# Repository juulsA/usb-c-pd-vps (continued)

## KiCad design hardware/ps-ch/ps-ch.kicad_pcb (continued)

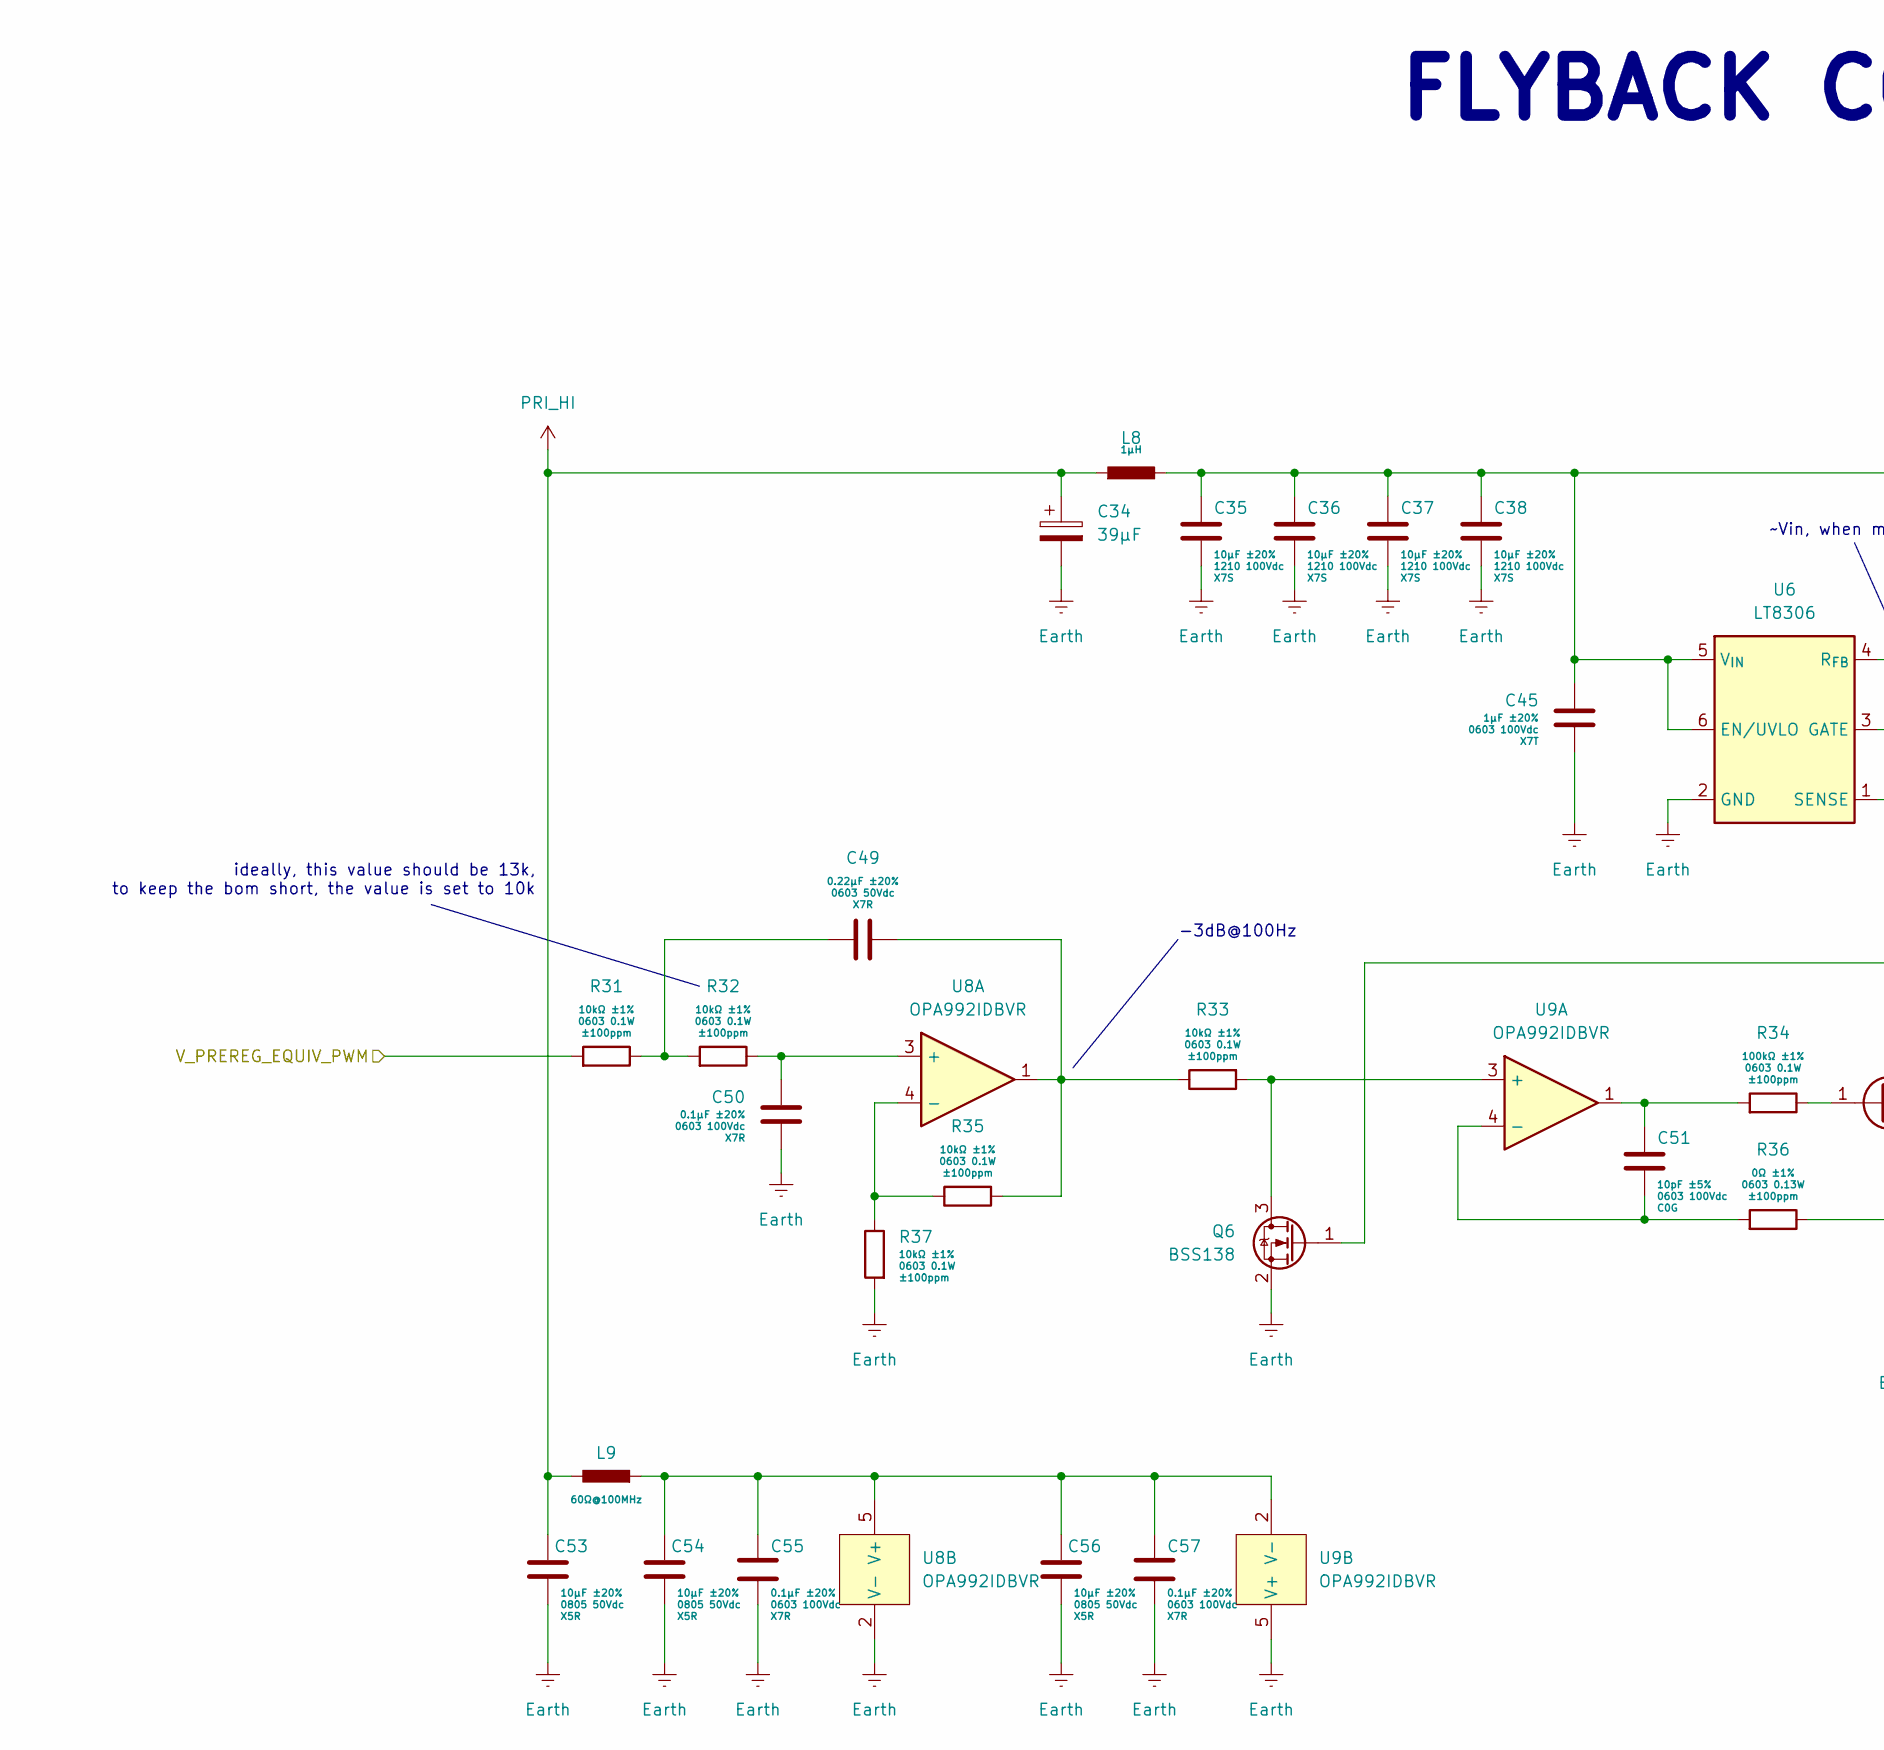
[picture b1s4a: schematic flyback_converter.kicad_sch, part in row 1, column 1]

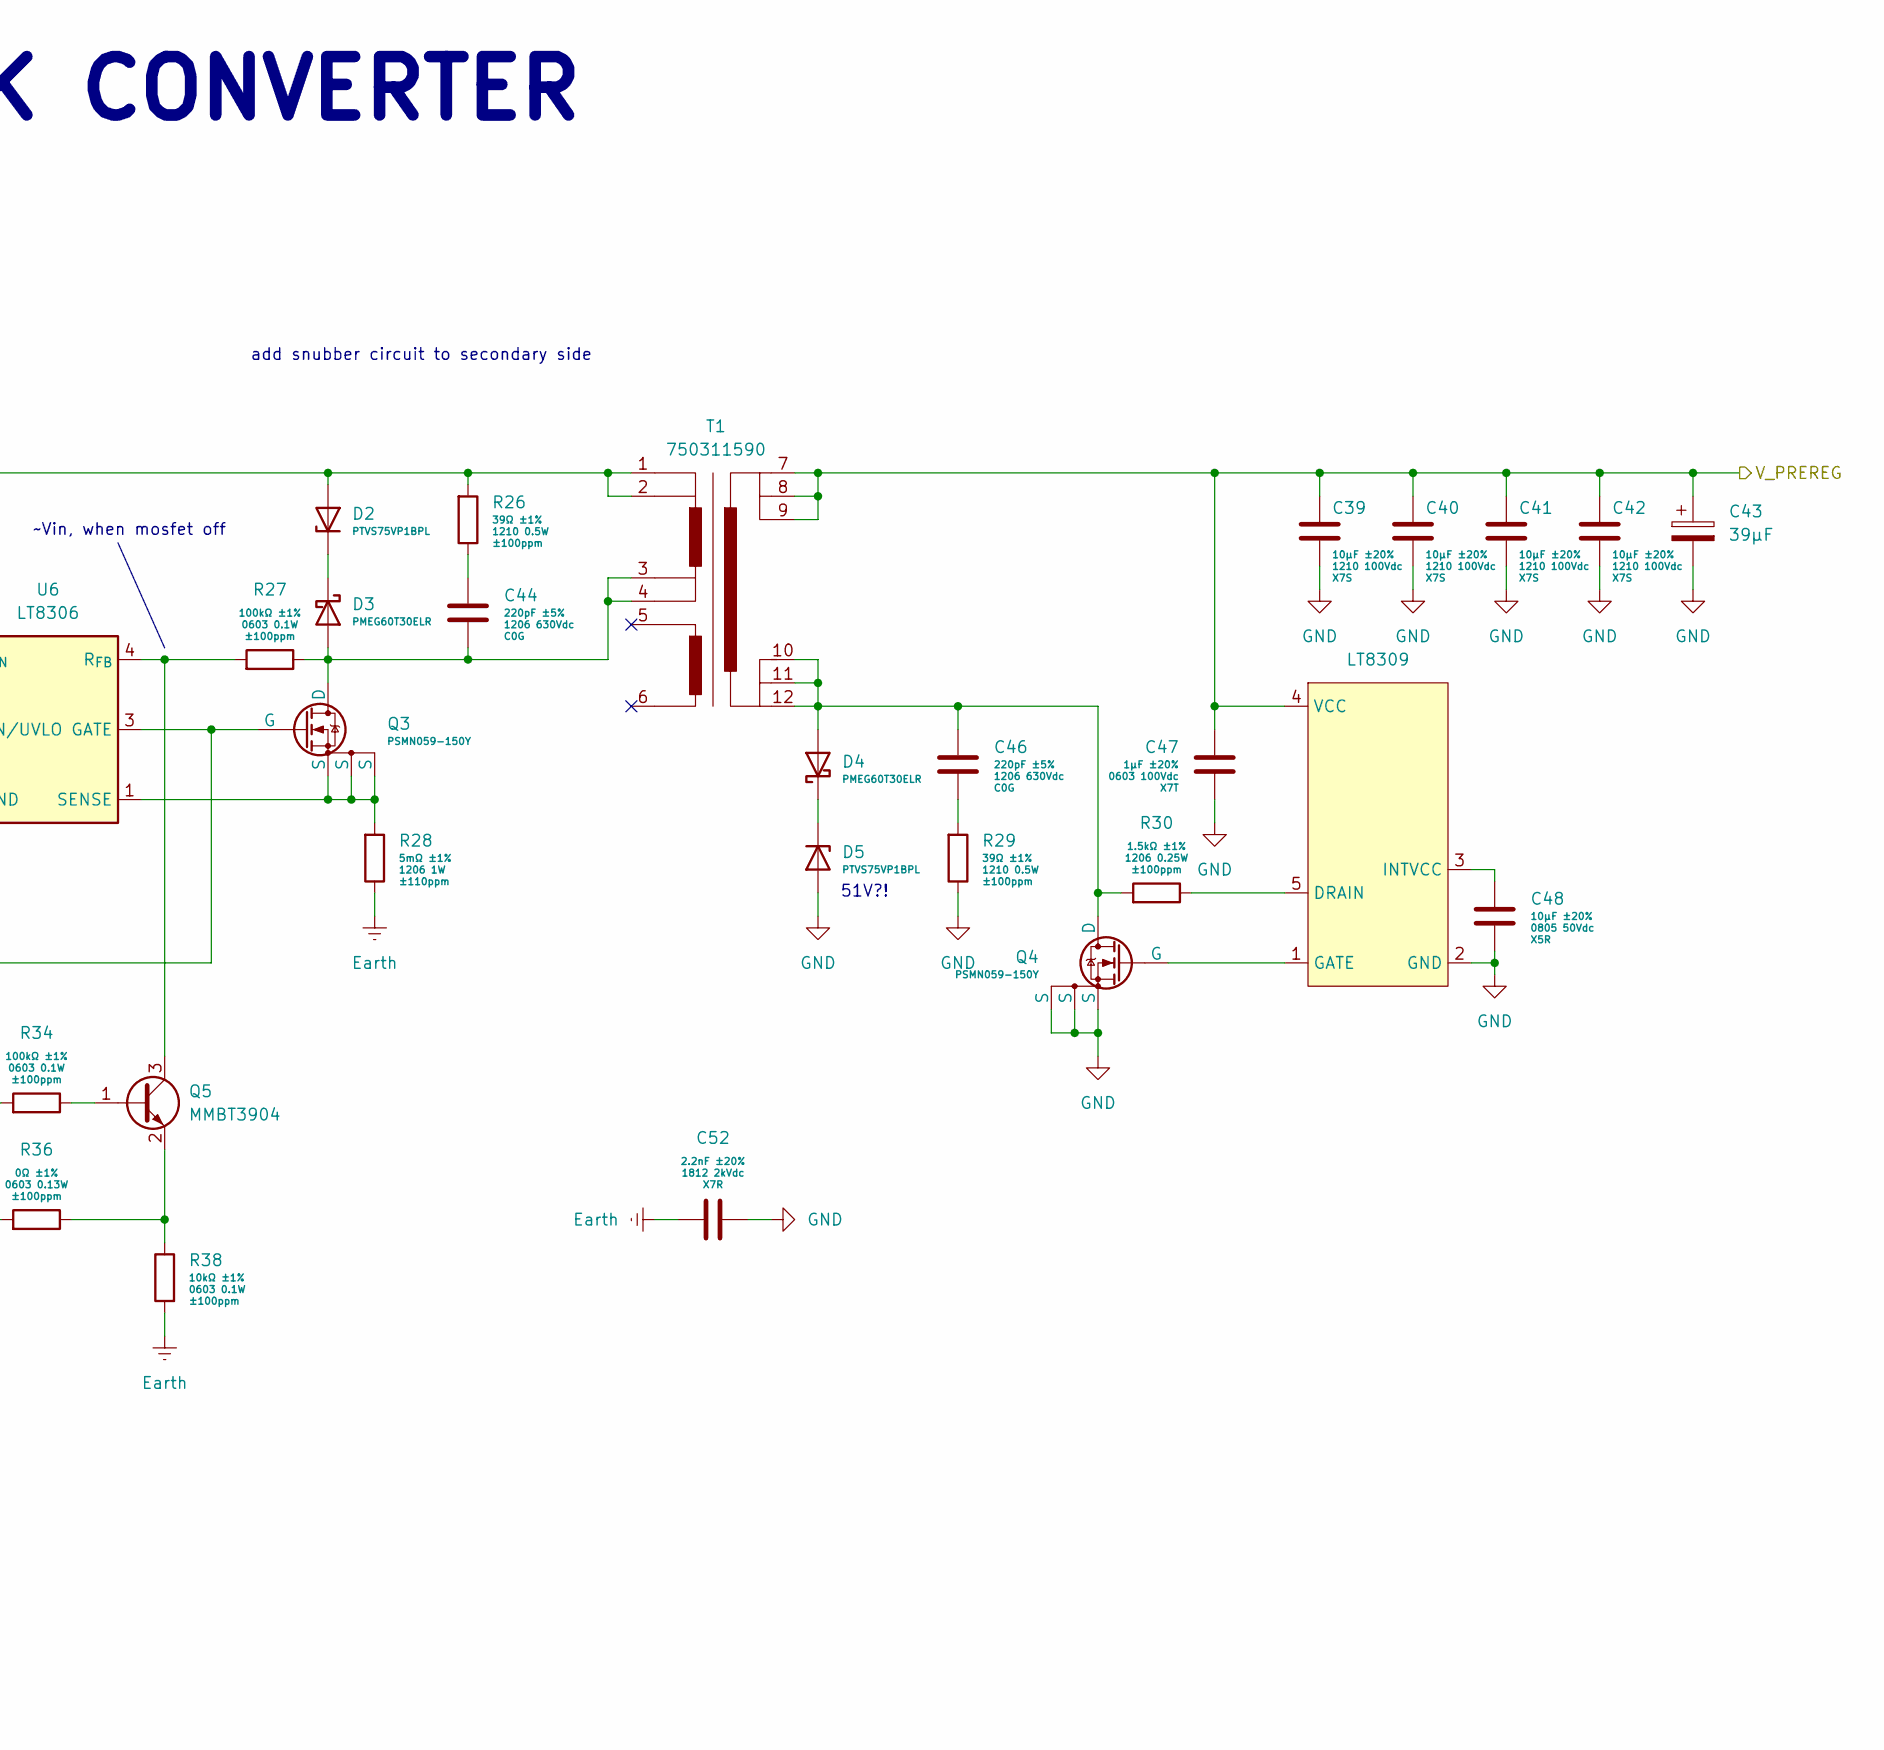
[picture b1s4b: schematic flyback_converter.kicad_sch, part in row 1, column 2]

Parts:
C34, C43: 39µF; CP_Elec_8x11.9; Manufacturer Part Number 875075855005
C35, C36, C37, C38, C39, C40, C41, C42: 10μF 1210 100Vdc X7S ±20%; C_1210_3225Metric; Manufacturer Part Number GRM32EC72A106ME05
C44, C46: 220pF 1206 630Vdc C0G ±5%; C_1206_3216Metric; Manufacturer Part Number GRM31A5C2J221JW01
C45, C47: 1μF 0603 100Vdc X7T ±20%; C_0603_1608Metric; Manufacturer Part Number GRM188D72A105ME01
C48, C53, C54, C56: 10μF 0805 50Vdc X5R ±20%; C_0805_2012Metric; Manufacturer Part Number GRM21BR61H106ME43
C49: 0.22μF 0603 50Vdc X7R ±20%; C_0603_1608Metric; Manufacturer Part Number GRM188R71H224MAC4
C50, C55, C57: 0.1μF 0603 100Vdc X7R ±20%; C_0603_1608Metric; Manufacturer Part Number GRM188R72A104MA35
C51: 10pF 0603 100Vdc C0G ±5%; C_0603_1608Metric; Manufacturer Part Number GCM1885C2A100JA16
C52: 2.2nF 1812 2kVdc X7R ±20%; C_1812_4532Metric; Manufacturer Part Number GR443QR73D222KW01
D2, D5: PTVS75VP1BPL; D_SOD-128; Manufacturer Part Number PTVS75VP1BPL
D3, D4: PMEG60T30ELR; Nexperia_CFP3_SOD-123W; Manufacturer Part Number PMEG60T30ELRX
L8: 1µH; WE-HCI_5040; Manufacturer Part Number 744316100
L9: 60Ω@100MHz; L_0603_1608Metric; Manufacturer Part Number 74279228600
Q3, Q4: PSMN059-150Y; SOT669; Manufacturer Part Number PSMN059-150Y,115
Q5: MMBT3904; SOT-23
Q6: BSS138; SOT-23
R26, R29: 39Ω 1210 0.5W ±1% ±100ppm/°C; R_1210_3225Metric; Manufacturer Part Number AC1210FR-0739RL
R27, R34: 100kΩ 0603 0.1W ±1% ±100ppm/°C; R_0603_1608Metric; Manufacturer Part Number AC0603FR-07100KL
R28: 5mΩ 1206 1W ±1% ±110ppm/°C; R_1206_3216Metric; Manufacturer Part Number WSLP12065L000FEA
R30: 1.5kΩ 1206 0.25W ±1% ±100ppm/°C; R_1206_3216Metric; Manufacturer Part Number AC1206FR-071K5L
R31, R32, R33, R35, R37, R38: 10kΩ 0603 0.1W ±1% ±100ppm/°C; R_0603_1608Metric; Manufacturer Part Number AC0603FR-0710KL
R36: 1kΩ 0603 0.1W ±1% ±100ppm/°C; R_0603_1608Metric; Manufacturer Part Number AC0603FR-070RL
T1: 750311590; EFD25; Manufacturer Part Number 750311590
U6: LT8306; TSOT-23-6
U7: LT8309; SOT-23-5; Manufacturer Part Number LT8309IS5#TRPBF
U8, U9: OPA992IDBVR; SOT-23-5; Manufacturer Part Number OPA992IDBVR

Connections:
/Flyback Converter/V_PREREG_EQUIV_PWM: R31.2; also elsewhere on the board
Earth: C34.2, C35.1, C36.1, C37.1, C38.1, C45.1, C50.1, C52.2, C53.1, C54.1, C55.1, C56.1, C57.1, Q6.2 (S), R28.1, R37.2, R38.2, U6.2 (GND), U8.2 (V-), U9.5 (V+); also elsewhere on the board
GND: C39.1, C40.1, C41.1, C42.1, C43.2, C47.2, C48.1, C52.1, D5.2 (A), Q4.1 (S), Q4.2 (S), Q4.3 (S), R29.1, U7.2 (GND); also elsewhere on the board
unnamed: C44.2, R26.1
unnamed: C46.1, R29.2
unnamed: C49.1, R33.1, R35.2, U8.1
unnamed: C49.2, R31.1, R32.2
unnamed: C51.2, R34.2, U9.1
unnamed: C35.2, C36.2, C37.2, C38.2, C45.2, D2.2 (A), L8.1, R26.2, T1.1, T1.2, U6.5 (V_{IN}), U6.6 (EN/UVLO)
unnamed: D2.1 (K), D3.1 (K)
unnamed: C44.1, D3.2 (A), Q3.5 (D), R27.1, T1.3, T1.4
unnamed: C46.2, D4.2 (A), Q4.5 (D), R30.2, T1.10, T1.11, T1.12
unnamed: D4.1 (K), D5.1 (K)
unnamed: Q3.4 (G), Q6.1 (G), U6.3 (GATE)
unnamed: Q4.4 (G), U7.1 (GATE)
unnamed: Q5.1 (B), R34.1
unnamed: Q5.3 (C), R27.2, U6.4 (R_{FB})
unnamed: Q5.2 (E), R36.1, R38.1
unnamed: Q6.3 (D), R33.2, U9.3 (+)
unnamed: Q3.1 (S), Q3.2 (S), Q3.3 (S), R28.2, U6.1 (SENSE)
unnamed: R30.1, U7.5 (DRAIN)
unnamed: C48.2, U7.3 (INTVCC)
unnamed: C50.2, R32.1, U8.3 (+)
unnamed: R35.1, R37.1, U8.4 (-)
unnamed: C54.2, C55.2, C56.2, C57.2, L9.1, U8.5 (V+), U9.2 (V-)
unnamed: C51.1, R36.2, U9.4 (-)
PRI_HI: C34.1, C53.2, L8.2, L9.2; also elsewhere on the board
VDC: C39.2, C40.2, C41.2, C42.2, C43.1, C47.1, T1.7, T1.8, T1.9, U7.4 (VCC); also elsewhere on the board

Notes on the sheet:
ideally, this value should be 13k, to keep the bom short, the value is set to 10k
51V?!
-3dB@100Hz
FLYBACK CONVERTER
add snubber circuit to secondary side
~Vin, when mosfet off

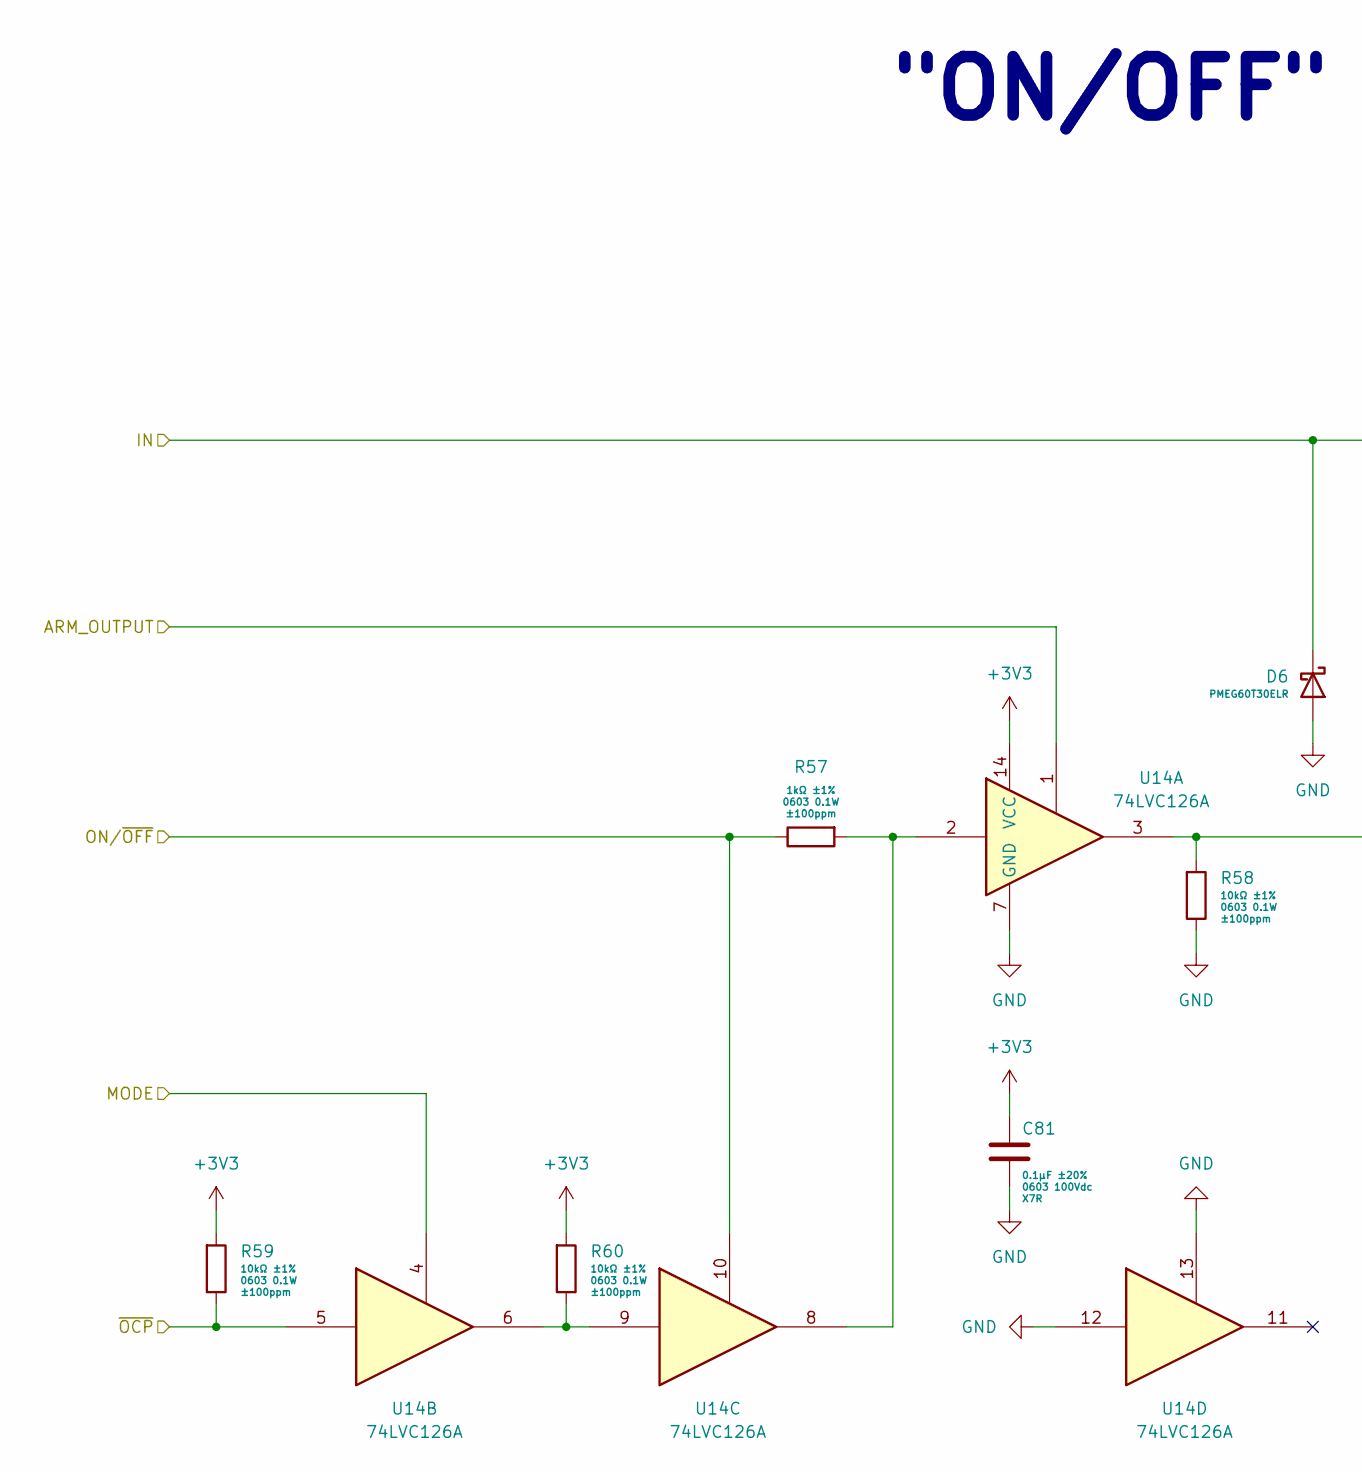
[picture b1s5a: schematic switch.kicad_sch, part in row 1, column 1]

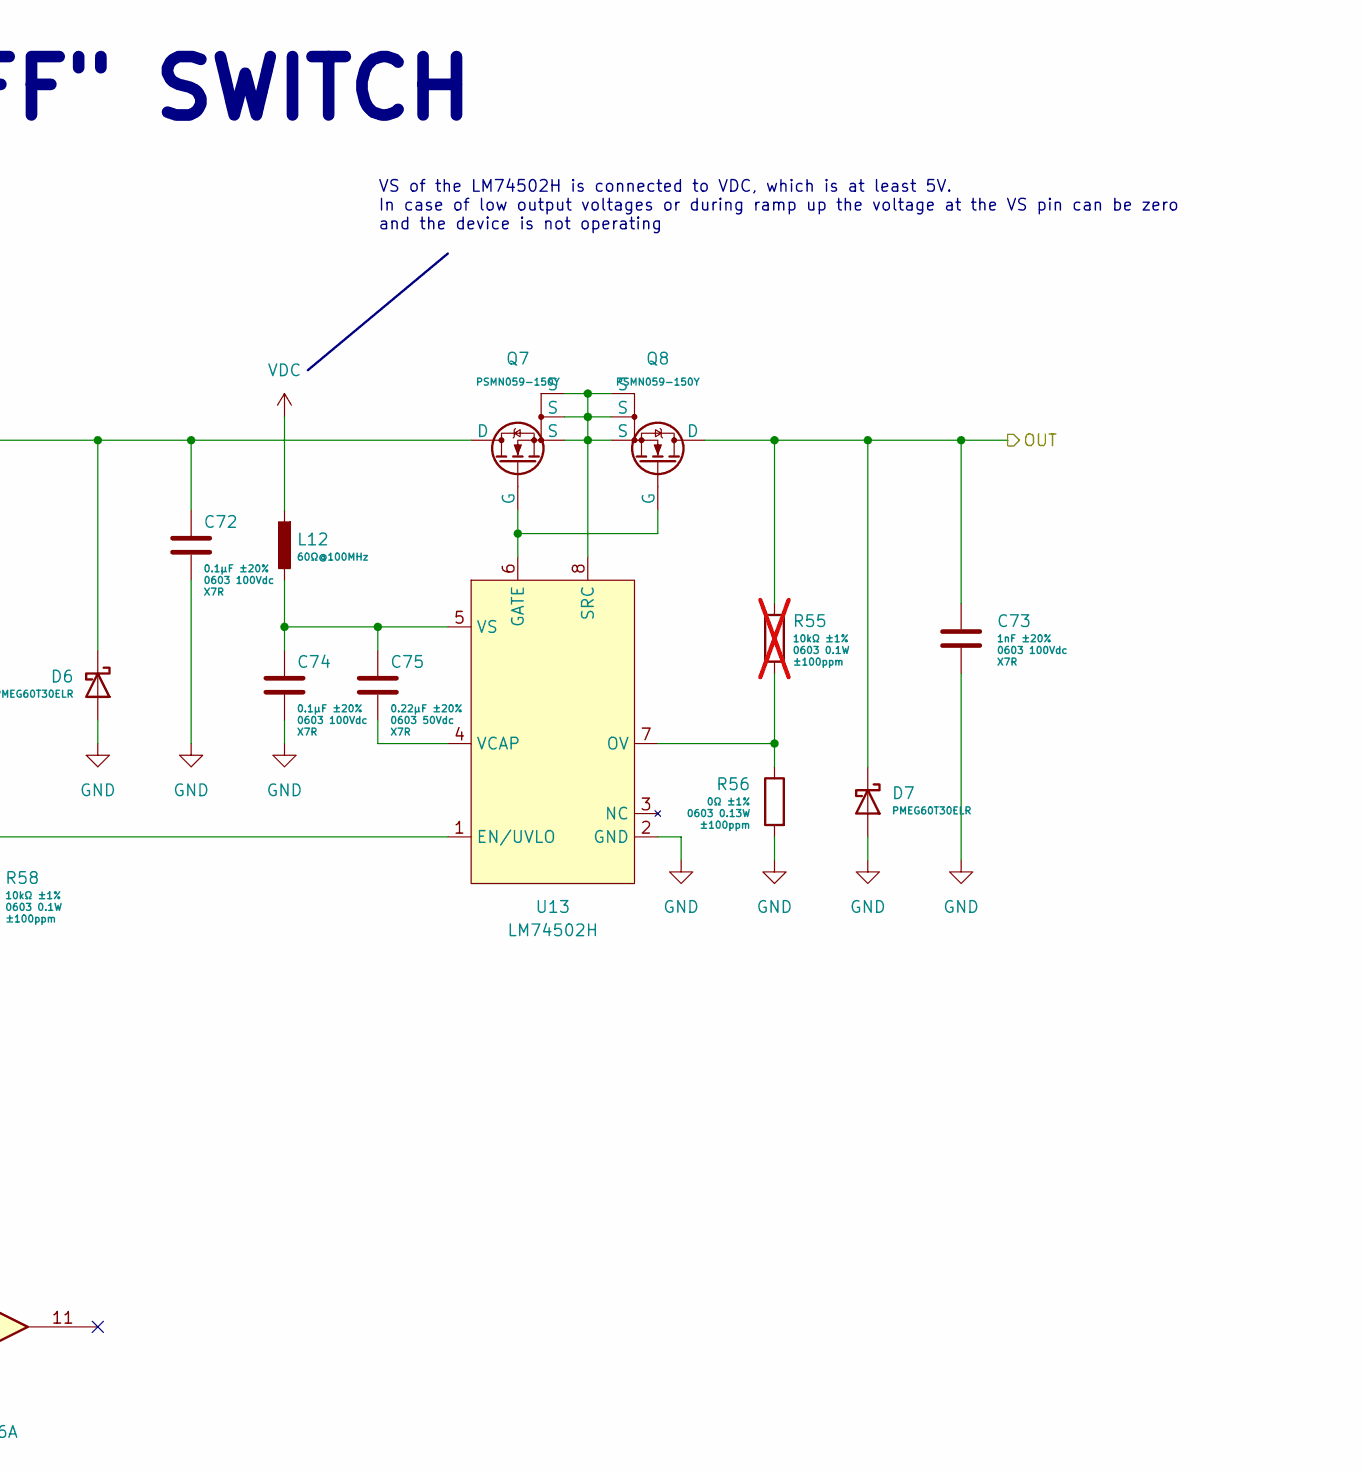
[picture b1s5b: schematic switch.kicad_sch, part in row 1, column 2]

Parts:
C72, C74, C81: 0.1μF 0603 100Vdc X7R ±20%; C_0603_1608Metric; Manufacturer Part Number GRM188R72A104MA35
C73: 1nF 0603 100Vdc X7R ±20%; C_0603_1608Metric; Manufacturer Part Number GCD188R72A102MA01
C75: 0.22μF 0603 50Vdc X7R ±20%; C_0603_1608Metric; Manufacturer Part Number GRM188R71H224MAC4
D6, D7: PMEG60T30ELR; Nexperia_CFP3_SOD-123W; Manufacturer Part Number PMEG60T30ELRX
L12: 60Ω@100MHz; L_0603_1608Metric; Manufacturer Part Number 74279228600
Q7, Q8: PSMN059-150Y; SOT669; Manufacturer Part Number PSMN059-150Y,115
R55: 10kΩ 0603 0.1W ±1% ±100ppm/°C; R_0603_1608Metric; Manufacturer Part Number AC0603FR-0710KL; not fitted
R56: 0Ω 0603 0.1W ±1% ±100ppm/°C; R_0603_1608Metric; Manufacturer Part Number AC0603FR-070RL
R57: 1kΩ 0603 0.1W ±1% ±100ppm/°C; R_0603_1608Metric; Manufacturer Part Number AC0603FR-071KL
R58, R59, R60: 10kΩ 0603 0.1W ±1% ±100ppm/°C; R_0603_1608Metric; Manufacturer Part Number AC0603FR-0710KL
U13: LM74502H; SOT-23-8; Manufacturer Part Number LM74502HDDFR
U14: 74LVC126A; TSSOP-14_4.4x5mm_P0.65mm; Manufacturer Part Number 74LVC126APW,118

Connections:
+3V3: C81.2, R59.2, R60.2, U14.14 (VCC); also elsewhere on the board
/Current Measurement/OUT: C72.2, D6.1 (K), Q7.5 (D); also elsewhere on the board
/Current Measurement/RESET: U14.4; also elsewhere on the board
/EN_OUTPUT: R57.1, U14.10; also elsewhere on the board
/Switch/ARM_OUTPUT: U14.1; also elsewhere on the board
/~OCP: R59.1, U14.5; also elsewhere on the board
GND: C72.1, C73.1, C74.1, C81.1, D6.2 (A), D7.2 (A), R56.2, R58.1, U13.2 (GND), U14.7 (GND), U14.12, U14.13; also elsewhere on the board
unnamed: Q7.4 (G), Q8.4 (G), U13.6 (GATE)
unnamed: R57.2, U14.2, U14.8
unnamed: R60.1, U14.6, U14.9
unnamed: R58.2, U13.1 (EN/UVLO), U14.3
unnamed: R55.2, R56.1, U13.7 (OV)
unnamed: Q7.1 (S), Q7.2 (S), Q7.3 (S), Q8.1 (S), Q8.2 (S), Q8.3 (S), U13.8 (SRC)
unnamed: C75.1, U13.4 (VCAP)
unnamed: C74.2, C75.2, L12.2, U13.5 (VS)
VDC: L12.1; also elsewhere on the board
VOUT: C73.2, D7.1 (K), Q8.5 (D), R55.1; also elsewhere on the board

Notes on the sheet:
VS of the LM74502H is connected to VDC, which is at least 5V. In case of low output voltages or during ramp up the voltage at the VS pin can be zero and the device is not operating
"ON/OFF" SWITCH

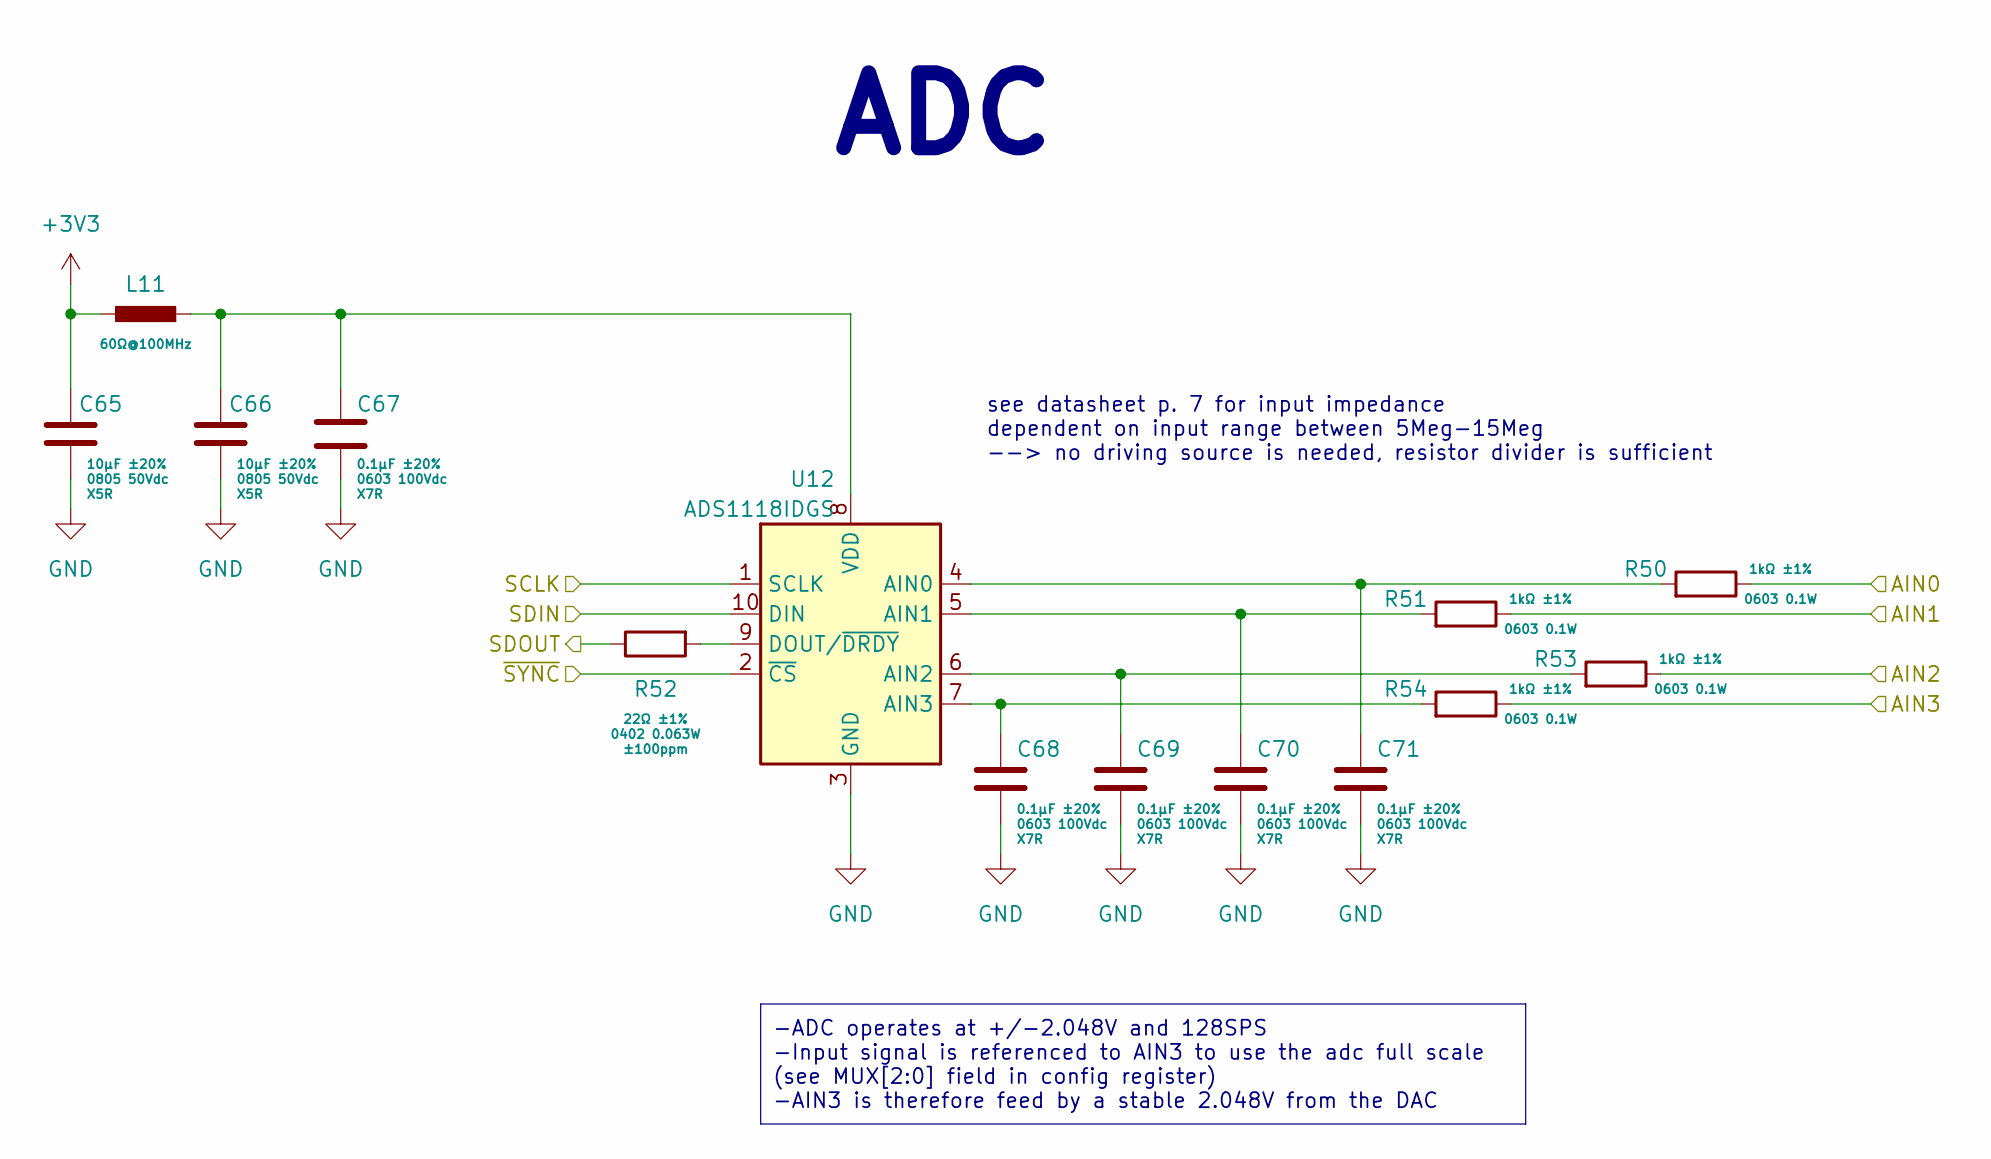
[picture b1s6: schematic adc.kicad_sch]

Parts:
C65, C66: 10μF 0805 50Vdc X5R ±20%; C_0805_2012Metric; Manufacturer Part Number GRM21BR61H106ME43
C67, C68, C69, C70, C71: 0.1μF 0603 100Vdc X7R ±20%; C_0603_1608Metric; Manufacturer Part Number GRM188R72A104MA35
L11: 60Ω@100MHz; L_0603_1608Metric; Manufacturer Part Number 74279228600
R50, R51, R53, R54: 1kΩ 0603 0.1W ±1% ±100ppm/°C; R_0603_1608Metric; Manufacturer Part Number AC0603FR-071KL
R52: 22Ω 0402 0.063W ±1% ±100ppm/°C; R_0402_1005Metric; Manufacturer Part Number AC0402FR-0722RL
U12: ADS1118IDGS; VSSOP-10_3x3mm_P0.5mm; Manufacturer Part Number ADS1118IDGSR

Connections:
+3V3: C65.2, L11.2; also elsewhere on the board
/ADC/AIN1: R51.1; also elsewhere on the board
/ADC_REF: R54.1; also elsewhere on the board
/AIN0: R50.1; also elsewhere on the board
/AIN2: R53.1; also elsewhere on the board
/MISO: R52.1; also elsewhere on the board
/MOSI: U12.10 (DIN); also elsewhere on the board
/SCK: U12.1 (SCLK); also elsewhere on the board
/~ADC_CS: U12.2 (~CS); also elsewhere on the board
GND: C65.1, C66.1, C67.1, C68.1, C69.1, C70.1, C71.1, U12.3 (GND); also elsewhere on the board
unnamed: C71.2, R50.2, U12.4 (AIN0)
unnamed: C70.2, R51.2, U12.5 (AIN1)
unnamed: C69.2, R53.2, U12.6 (AIN2)
unnamed: C68.2, R54.2, U12.7 (AIN3)
unnamed: R52.2, U12.9 (DOUT/~DRDY)
unnamed: C66.2, C67.2, L11.1, U12.8 (VDD)

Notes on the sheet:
see datasheet p. 7 for input impedance dependent on input range between 5Meg-15Meg --> no driving source is needed, resistor divider is sufficient
ADC
-ADC operates at +/-2.048V and 128SPS -Input signal is referenced to AIN3 to use the adc full scale (see MUX[2:0] field in config register) -AIN3 is therefore feed by a stable 2.048V from the DAC

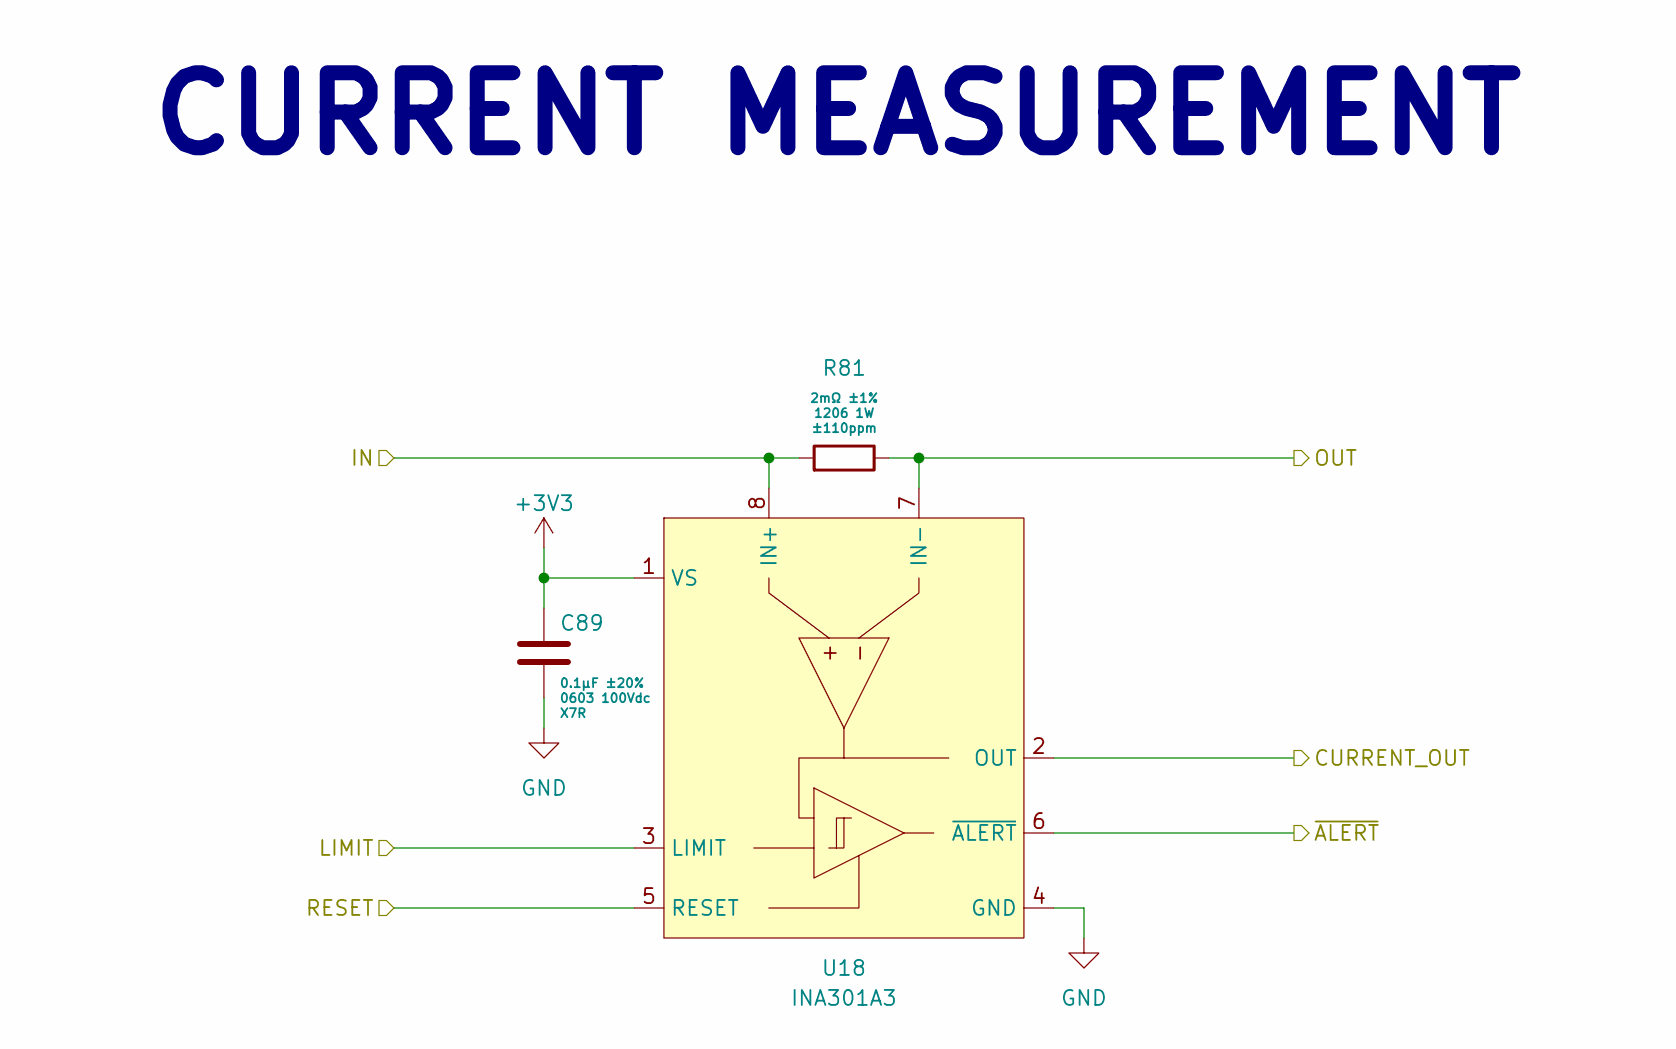
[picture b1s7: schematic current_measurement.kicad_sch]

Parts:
C89: 0.1μF 0603 100Vdc X7R ±20%; C_0603_1608Metric; Manufacturer Part Number GRM188R72A104MA35
R81: 2mΩ 1206 1W ±1% ±50ppm/°C; R_1206_3216Metric; Manufacturer Part Number CRF1206FZR002ELF
U18: INA301A3; VSSOP-8_3x3mm_P0.65mm; Manufacturer Part Number INA301A3IDGKR

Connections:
+3V3: C89.2, U18.1 (VS); also elsewhere on the board
/AIN2: U18.2 (OUT); also elsewhere on the board
/Current Measurement/IN: R81.2, U18.8 (IN+); also elsewhere on the board
/Current Measurement/LIMIT: U18.3 (LIMIT); also elsewhere on the board
/Current Measurement/OUT: R81.1, U18.7 (IN-); also elsewhere on the board
/Current Measurement/RESET: U18.5 (RESET); also elsewhere on the board
/~OCP: U18.6 (~ALERT); also elsewhere on the board
GND: C89.1, U18.4 (GND); also elsewhere on the board

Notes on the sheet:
CURRENT MEASUREMENT

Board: 2 copper layers, 232 parts (0 on the bottom side), 130 nets, no tracks yet.

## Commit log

2025-06-28 Create usb-c-pd-vps.ipynb
    - initial commit
    - added first basic calculation
2025-06-28 Update usb-c-pd-vps.ipynb
    - changed x-limits
2025-06-28 Update usb-c-pd-vps.ipynb
    - added switching frequency calculation
2025-06-30 Update usb-c-pd-vps.ipynb
    - updated calculations for n_ps=1.5
2025-06-30 Create pwr_spl_concept.png
    - added power supply concept
2025-06-30 created kicad projects
2025-06-30 Create LICENSE
2025-07-01 started ps-ch schematics
2025-07-01 added lm61495
2025-07-03 added equations (unordered)
2025-07-05 updated calculations
2025-07-05 cleaned up code
2025-07-05 changed voltage generation style
    updated all equations
2025-07-06 added AD5693RB
2025-07-06 added current limiting circuit
2025-07-07 added auto current limiter and auto voltage adjustment
2025-07-08 changed vsense circuit
2025-07-09 added AD5693R
2025-07-09 changed vout error correction
2025-07-10 simplified circuit
    -removed opamps
2025-07-13 added opa992
2025-07-18 added digital isolators
2025-07-20 -added 3V3 power supply and STM32
2025-07-20 defined gpios
2025-07-20 added series resistors for npn transistors
2025-07-27 Update ps-ch.kicad_sch
    -added 2nd digital isolator
2025-07-27 Update ps-ch.kicad_sch
    connected gpios
2025-07-27 updated porject description
    - updated readme
    - renamed gpios (stm32)
2025-07-27 Update ps-ch.kicad_sch
    - added testpoints to oscx_x
2025-07-27 edited schematics
    - selected npn/pnp
    - added connector for swd interface
2025-08-01 added components
2025-08-09 started making hierachical design
2025-08-09 created voltage regulation
2025-08-10 did some wiring
2025-08-10 more wiring
    - updated stm32 pinout
    - added load switch
2025-08-16 drawn enabled circuit
2025-08-16 Update switch.kicad_sch
    - connected nmos driver to vdc
2025-08-24 added 74LVC126A
2025-09-14 - added component values/part numbers
2025-09-22 calculated voltage dividers
2025-09-23 added calculations and component values
2025-09-23 calculated voltage correction
2025-09-24 wired adc/added resolutions
2025-09-24 parameterized flyback converter
2025-09-25 changed voltage regulation (preregulator)
2025-09-25 improved circuit
2025-09-25 added discharge resistors
2025-09-25 assigned footprints
2025-09-28 added snubber circuit components
2025-09-30 changed voltage sensing circuit
2025-10-03 created and assigned footprints
2025-10-03 first pcb sync
2025-10-05 removed cmc, replaced input/output connectors
2025-10-05 started floorplanning
